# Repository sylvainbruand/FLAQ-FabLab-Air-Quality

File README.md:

# FLAQ XIAO — FabLab Air Quality

Projet académique de contrôle de la qualité de l’air dans les FabLabs, réalisé
avec une **Seeed Studio XIAO ESP32S3**. La carte acquiert les
capteurs, affiche les mesures sur OLED, enregistre l’historique sur microSD et
héberge elle-même un dashboard accessible depuis un téléphone ou un ordinateur.

[▶ Voir la vidéo de présentation FLAQ](FLAQ.mp4) — version MP4 de `FLAQ.avi`.

## Fonctions incluses

- actualisation des mesures toutes les 10 secondes ;
- lecture du SGP40 toutes les secondes avec compensation DHT20 ;
- trois graphiques avec axes indépendants ;
- moyenne glissante PM2.5 sur 24 heures ;
- indice intérieur FLAQ du vert au rouge ;
- alarme confirmée sur buzzer passif au niveau rouge ;
- journal persistant des dépassements avec durée, moyenne et maximum ;
- synthèse quotidienne et export CSV depuis le dashboard ;
- horodatage par RTC Grove PCF85063 ;
- correction NTP automatique lorsque le réseau donne accès à Internet ;
- point d’accès `FLAQ-XIAO` si aucun Wi-Fi n’est configuré ou disponible ;
- reprise de l’historique des dernières 24 heures après redémarrage ;
- navigation manuelle entre les quatre pages OLED avec le bouton Grove ;
- extinction de l’OLED après 20 secondes sans appui et réveil automatique ;
- déclaration manuelle d’une ventilation avec un second bouton Grove ;
- signalement de la ventilation sur le dashboard ;
- bandes temporelles claires sur les graphes pendant les périodes ventilées.

## Matériel

| Fonction | Référence | Connexion |
|---|---|---|
| Carte | Seeed Studio XIAO ESP32S3 | — |
| Hub | Grove 8-Channel I²C Hub TCA9548A | `D4/SDA`, `D5/SCL`, adresse `0x70` |
| CO₂ | SCD30 | I²C `0x61` |
| Particules | HM3301 | I²C `0x40` |
| VOC | SGP40 | I²C `0x59` |
| HCHO indicatif | Grove HCHO WSP2110 | analogique `D0`, via pont diviseur |
| Température/humidité | DHT20 | I²C `0x38` |
| Horloge | RTC Grove PCF85063 | I²C `0x51` |
| Affichage | OLED SSD1306 128×64 | I²C `0x3C` |
| Alarme | Grove Passive Buzzer 107020109 | `D1` |
| Navigation OLED | Grove Button (P) 111020000 | port `D7 / UART` |
| Ventilation | Grove Button (P) 111020000 | port `D0 / A0` |
| Stockage | Adafruit MicroSD Breakout+ 254 | SPI, CS sur `D2` |

Le câblage détaillé se trouve dans
[flaq_xiao/CABLAGE.md](flaq_xiao/CABLAGE.md).

Au démarrage, le firmware ouvre automatiquement les huit canaux du TCA9548A.
Cette configuration est possible car chaque capteur utilise une adresse I²C
différente. Elle se règle avec `FLAQ_I2C_MUX_*` dans `config.example.h`.

## Préparation de l’Arduino IDE

1. Installer le paquet de cartes **esp32 by Espressif Systems**.
2. Sélectionner **XIAO_ESP32S3**.
3. Activer la PSRAM en mode **OPI PSRAM**.
4. Sélectionner une taille Flash de **8 MB**.
5. Installer les bibliothèques :
   - U8g2 ;
   - Adafruit SGP40 Sensor, avec ses dépendances ;
   - SparkFun SCD30 Arduino Library ;
   - DHT20 de Rob Tillaart.

Le HM3301 est lu directement par le firmware via `Wire`, afin d’éviter
l’incompatibilité du type `u32` présente dans la bibliothèque Seeed 1.0.2 avec
les versions ESP32 récentes. En cas de trame incomplète ou de checksum invalide,
la lecture est retentée trois fois et le capteur est automatiquement replacé en
mode I2C. Les concentrations utilisées sont les valeurs « environnement
atmosphérique » du HM3301.

Les bibliothèques `WiFi`, `WebServer`, `ESPmDNS`, `SD`, `SPI` et `Wire` sont
fournies par le paquet ESP32.

## Configuration Wi-Fi

Le projet fonctionne immédiatement sans identifiants : la carte crée le réseau
`FLAQ-XIAO`, protégé par le mot de passe `flaq-air`. Une fois connecté à ce
réseau, ouvrir `http://192.168.4.1`.

Pour connecter la station au réseau local :

1. copier `config.h.example` sous le nom `config.h` ;
2. renseigner le nom et le mot de passe Wi-Fi ;
3. téléverser à nouveau le programme.

Le dashboard devient alors accessible à l’adresse IP affichée sur l’OLED et,
si le réseau l’autorise, à `http://flaq-xiao.local`.

`config.h` est ignoré par Git pour ne pas publier le mot de passe.

## Carte microSD

Utiliser une microSD High Endurance de 32 Go formatée en FAT32. La station crée :

- `/data/AAAAMMJJ.csv` : mesures d’une journée ;
- `/events.csv` : dépassements terminés.

La fenêtre glissante est maintenue en PSRAM. Au redémarrage, les fichiers du
jour courant et du jour précédent sont relus afin de reconstruire les dernières
24 heures, la moyenne PM2.5 et les périodes de ventilation. La colonne
`ventilation` vaut `1` lorsque la fenêtre ou la porte a été déclarée ouverte.

## Seuils

Tous les seuils se trouvent dans `config.example.h` et peuvent être redéfinis
dans `config.h`. L’indice global correspond au paramètre instantané le plus
défavorable parmi CO₂, VOC, HCHO estimé, PM2.5 et PM10.

Une alerte ou un événement nécessite trois mesures consécutives au-dessus du
seuil. Le retour utilise un seuil plus bas et trois confirmations, ce qui évite
les oscillations autour d’une limite.

Le seuil de la moyenne PM2.5 sur 24 heures produit un événement distinct. Il
n’est activé que lorsque la station dispose d’au moins 23 heures d’historique.

Ces seuils constituent un indicateur pédagogique FLAQ de qualité de l’air
intérieur ; ils ne remplacent pas un dispositif réglementaire ou certifié.

## Particularités du WSP2110

Le WSP2110 est désactivé par défaut avec `FLAQ_WSP2110_ENABLED 0`. Dans cet
état, D0 n'est pas lu, le dashboard affiche « non installé », le HCHO est
ignoré par l'indice et aucune alerte HCHO n'est créée. Quand le capteur et son
pont diviseur sont prêts, définir `FLAQ_WSP2110_ENABLED 1` dans `config.h`.

Le WSP2110 est un capteur MOS sensible à plusieurs gaz et solvants. La valeur
« HCHO estimé » en ppm sert donc à suivre une tendance après étalonnage ; ce
n’est pas une mesure sélective ou certifiée du formaldéhyde. Le capteur demande
au moins 120 heures de préchauffage avant son étalonnage initial.

Le module Grove fonctionne en 5 V alors que l’entrée analogique du XIAO est en
3,3 V. Sa sortie doit obligatoirement passer par le pont 15 kΩ / 20 kΩ décrit
dans `flaq_xiao/CABLAGE.md`. La constante `FLAQ_WSP2110_R0_RATIO` doit ensuite
être ajustée dans `config.h` avec la valeur obtenue en air propre stabilisé. Le
moniteur série affiche `WSP_Rs` et `ADC` pour faciliter cette opération.

## API embarquée

| Route | Rôle |
|---|---|
| `/` | dashboard |
| `/logo.png` | logo FLAQ et favicon |
| `/api/live` | dernière mesure et état technique |
| `/api/history?since=...&max=900` | historique sous-échantillonné |
| `/api/events?max=200` | journal des dépassements |
| `/api/events.csv` | téléchargement CSV |
| `/api/health` | mémoire et disponibilité du serveur |

## Organisation du dépôt

- [`flaq_xiao/`](flaq_xiao/) : station autonome XIAO ESP32S3 ;

## Fichiers du projet XIAO

- `flaq_xiao/flaq_xiao.ino` : firmware complet ;
- `flaq_xiao/dashboard.h` : interface web embarquée sans dépendance Internet ;
- `flaq_xiao/config.example.h` : valeurs par défaut et seuils ;
- `flaq_xiao/config.h.example` : modèle de configuration Wi-Fi ;
- `flaq_xiao/CABLAGE.md` : raccordement pas à pas ;
- `flaq_xiao/VERIFICATION.md` : procédure de mise en service.

## Vues du projet FLAQ

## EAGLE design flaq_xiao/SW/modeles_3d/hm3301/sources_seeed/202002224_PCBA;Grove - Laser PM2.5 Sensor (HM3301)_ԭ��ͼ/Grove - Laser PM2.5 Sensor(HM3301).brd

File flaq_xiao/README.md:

# FLAQ XIAO — FabLab Air Quality

Projet académique de contrôle de la qualité de l’air dans les FabLabs, réalisé
avec une **Seeed Studio XIAO ESP32S3**. La carte acquiert les
capteurs, affiche les mesures sur OLED, enregistre l’historique sur microSD et
héberge elle-même un dashboard accessible depuis un téléphone ou un ordinateur.

## Fonctions incluses

- actualisation des mesures toutes les 10 secondes ;
- lecture du SGP40 toutes les secondes avec compensation DHT20 ;
- trois graphiques avec axes indépendants ;
- moyenne glissante PM2.5 sur 24 heures ;
- indice intérieur FLAQ du vert au rouge ;
- alarme confirmée sur buzzer passif au niveau rouge ;
- journal persistant des dépassements avec durée, moyenne et maximum ;
- synthèse quotidienne et export CSV depuis le dashboard ;
- horodatage par RTC Grove PCF85063 ;
- correction NTP automatique lorsque le réseau donne accès à Internet ;
- point d’accès `FLAQ-XIAO` si aucun Wi-Fi n’est configuré ou disponible ;
- reprise de l’historique des dernières 24 heures après redémarrage.
- navigation manuelle entre les quatre pages OLED avec le bouton Grove ;
- extinction de l’OLED après 20 secondes sans appui et réveil automatique.
- déclaration manuelle d’une ventilation avec un second bouton Grove ;
- mode mute basculé en appuyant sur les deux boutons en même temps ;
- signalement de la ventilation sur le dashboard et éclaircissement des graphes.
- bandes temporelles claires sur les graphes pendant les périodes ventilées.

## Matériel

| Fonction | Référence | Connexion |
|---|---|---|
| Carte | Seeed Studio XIAO ESP32S3 | — |
| Hub | Grove 8-Channel I²C Hub TCA9548A | `D4/SDA`, `D5/SCL`, adresse `0x70` |
| CO₂ | SCD30 | I²C `0x61` |
| Particules | HM3301 | I²C `0x40` |
| VOC | SGP40 | I²C `0x59` |
| HCHO indicatif | Grove HCHO WSP2110 | analogique `D0`, via pont diviseur |
| Température/humidité | DHT20 | I²C `0x38` |
| Horloge | RTC Grove PCF85063 | I²C `0x51` |
| Affichage | OLED SSD1306 128×64 | I²C `0x3C` |
| Alarme | Grove Passive Buzzer 107020109 | `D1` |
| Navigation OLED + ventilation | Grove Dual Button | port `D7 / UART` (`D7` + `D6`) |
| Stockage | Adafruit MicroSD Breakout+ 254 | SPI, CS sur `D2` |

Le câblage détaillé se trouve dans [CABLAGE.md](CABLAGE.md).

Au démarrage, le firmware ouvre automatiquement les huit canaux du TCA9548A.
Cette configuration est possible car chaque capteur utilise une adresse I²C
différente. Elle se règle avec `FLAQ_I2C_MUX_*` dans `config.example.h`.

## Préparation de l’Arduino IDE

1. Installer le paquet de cartes **esp32 by Espressif Systems**.
2. Sélectionner **XIAO_ESP32S3**.
3. Activer la PSRAM en mode **OPI PSRAM**.
4. Sélectionner une taille Flash de **8 MB**.
5. Installer les bibliothèques :
   - U8g2 ;
   - Adafruit SGP40 Sensor, avec ses dépendances ;
   - SparkFun SCD30 Arduino Library ;
   - DHT20 de Rob Tillaart.

Le HM3301 est lu directement par le firmware via `Wire`, afin d’éviter
l’incompatibilité du type `u32` présente dans la bibliothèque Seeed 1.0.2 avec
les versions ESP32 récentes. En cas de trame incomplète ou de checksum invalide,
la lecture est retentée trois fois et le capteur est automatiquement replacé en
mode I2C. Les concentrations utilisées sont les valeurs « environnement
atmosphérique » du HM3301.

Les bibliothèques `WiFi`, `WebServer`, `ESPmDNS`, `SD`, `SPI` et `Wire` sont
fournies par le paquet ESP32.

## Configuration Wi-Fi

Le projet fonctionne immédiatement sans identifiants : la carte crée le réseau
`FLAQ-XIAO`, protégé par le mot de passe `flaq-air`. Une fois connecté à ce
réseau, ouvrir `http://192.168.4.1`.

Pour connecter la station au réseau local :

1. copier `config.h.example` sous le nom `config.h` ;
2. renseigner les noms et mots de passe des réseaux Wi-Fi dans
   `FLAQ_WIFI_NETWORKS` (une ligne par réseau) ;
3. téléverser à nouveau le programme.

Au démarrage, l’OLED affiche la liste configurée. Le bouton sur D7 passe au
réseau suivant et le bouton sur D6 valide le réseau affiché. Après la
validation, les deux boutons reprennent automatiquement leur fonctionnement
normal (pages OLED et ventilation). Si la connexion choisie échoue, la station
crée comme auparavant le point d’accès `FLAQ-XIAO`.

Le dashboard devient alors accessible à l’adresse IP affichée sur l’OLED et,
si le réseau l’autorise, à `http://flaq-xiao.local`.

`config.h` est ignoré par Git pour ne pas publier le mot de passe.

## Carte microSD

Utiliser une microSD High Endurance de 32 Go formatée en FAT32. La station crée :

- `/data/AAAAMMJJ.csv` : mesures d’une journée ;
- `/events.csv` : dépassements terminés.

La fenêtre glissante est maintenue en PSRAM. Au redémarrage, les fichiers du
jour courant et du jour précédent sont relus afin de reconstruire les dernières
24 heures, la moyenne PM2.5 et les périodes de ventilation. La colonne
`ventilation` vaut `1` lorsque la fenêtre ou la porte a été déclarée ouverte.

## Seuils

Tous les seuils se trouvent dans `config.example.h` et peuvent être redéfinis
dans `config.h`. L’indice global correspond au paramètre instantané le plus
défavorable parmi CO₂, VOC, HCHO estimé, PM2.5 et PM10.

Une alerte ou un événement nécessite trois mesures consécutives au-dessus du
seuil. Le retour utilise un seuil plus bas et trois confirmations, ce qui évite
les oscillations autour d’une limite.

Le seuil de la moyenne PM2.5 sur 24 heures produit un événement distinct. Il
n’est activé que lorsque la station dispose d’au moins 23 heures d’historique.

Ces seuils constituent un indicateur pédagogique FLAQ de qualité de l’air
intérieur ; ils ne remplacent pas un dispositif réglementaire ou certifié.

## Particularités du WSP2110

Le WSP2110 est lu sur D0 mais reste optionnel. S’il n’est pas branché, ou tant
qu’aucune lecture valide n’est détectée, le dashboard affiche « indisponible »,
le HCHO est ignoré par l’indice et aucune alerte HCHO n’est créée. Cette absence
n’empêche ni le démarrage ni le fonctionnement des autres capteurs.

Le WSP2110 est un capteur MOS sensible à plusieurs gaz et solvants. La valeur
« HCHO estimé » en ppm sert donc à suivre une tendance après étalonnage ; ce
n’est pas une mesure sélective ou certifiée du formaldéhyde. Le capteur demande
au moins 120 heures de préchauffage avant son étalonnage initial.

Le module Grove fonctionne en 5 V alors que l’entrée analogique du XIAO est en
3,3 V. Sa sortie doit obligatoirement passer par le pont 15 kΩ / 20 kΩ décrit
dans `CABLAGE.md`. La constante `FLAQ_WSP2110_R0_RATIO` doit ensuite être
ajustée dans `config.h` avec la valeur obtenue en air propre stabilisé. Le
moniteur série affiche `WSP_Rs` et `ADC` pour faciliter cette opération.

## API embarquée

| Route | Rôle |
|---|---|
| `/` | dashboard |
| `/logo.png` | logo FLAQ et favicon |
| `/api/live` | dernière mesure et état technique |
| `/api/history?since=...&max=900` | historique sous-échantillonné |
| `/api/events?max=200` | journal des dépassements |
| `/api/events.csv` | téléchargement CSV |
| `/api/health` | mémoire et disponibilité du serveur |

## Fichiers du projet

- `flaq_xiao.ino` : firmware complet ;
- `dashboard.h` : interface web embarquée sans dépendance Internet ;
- `flaq_logo.png` et `flaq_logo.h` : logo optimisé et ressource embarquée ;
- `config.example.h` : valeurs par défaut et seuils ;
- `config.h.example` : modèle de configuration Wi-Fi ;
- `CABLAGE.md` : raccordement pas à pas ;
- `VERIFICATION.md` : procédure de mise en service.

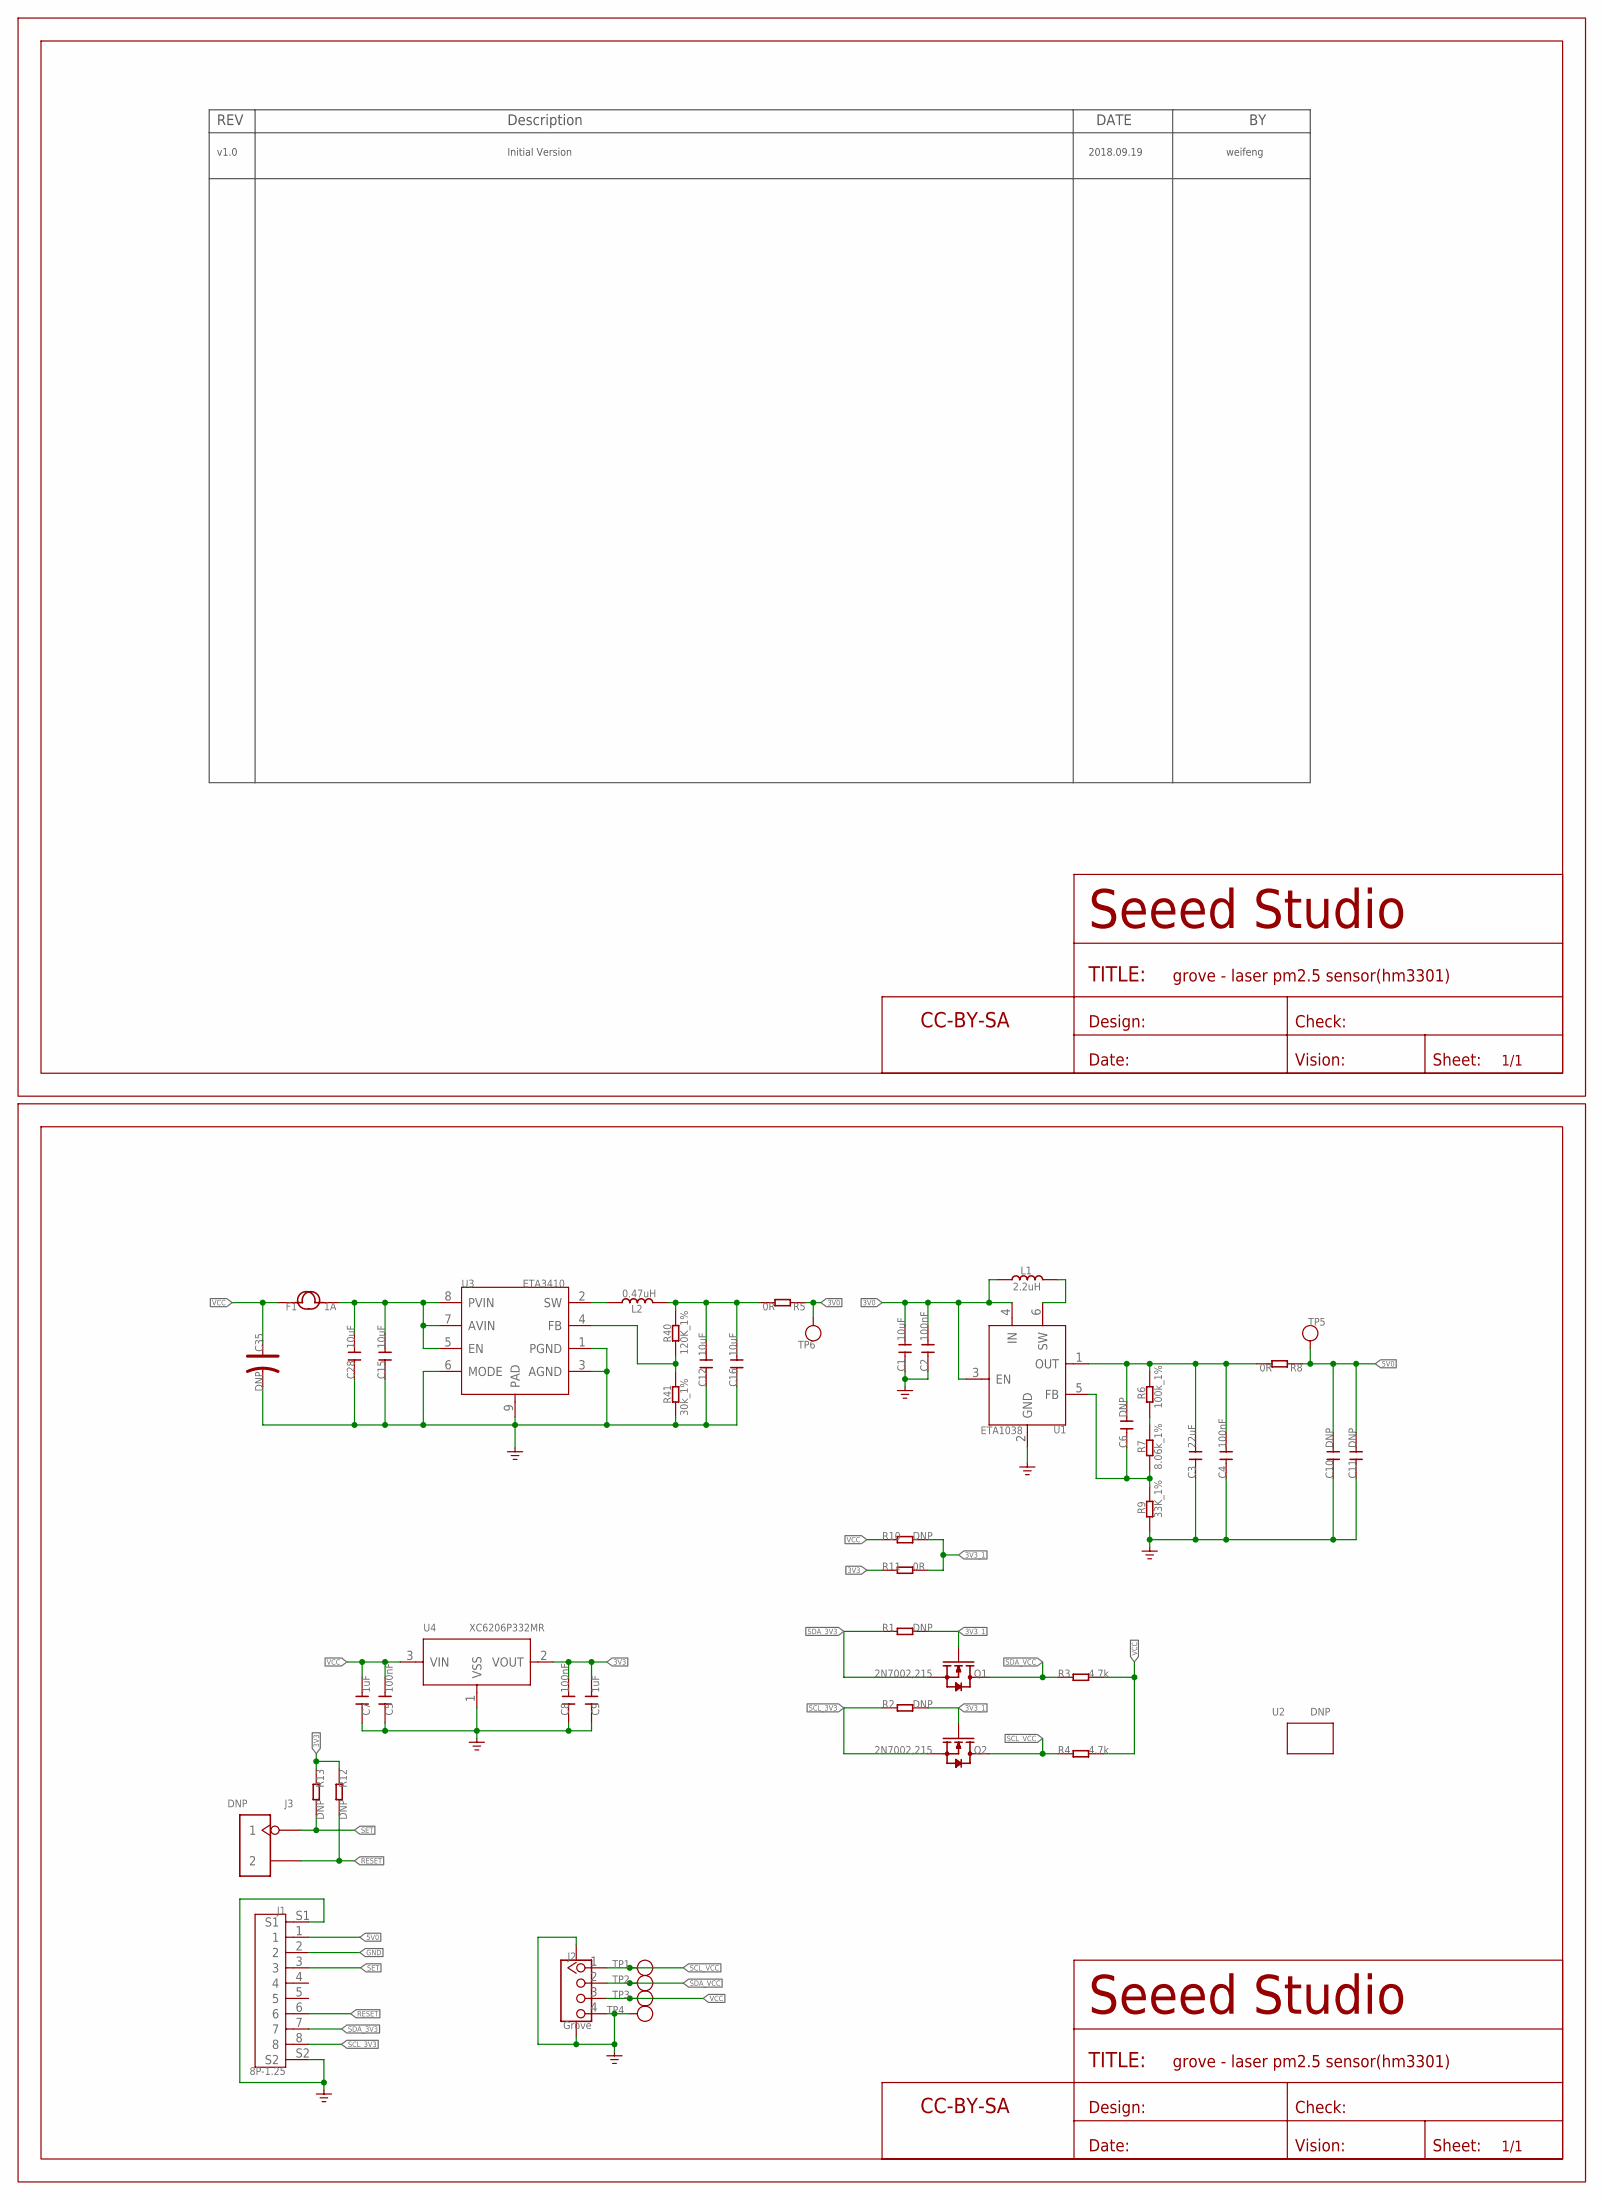
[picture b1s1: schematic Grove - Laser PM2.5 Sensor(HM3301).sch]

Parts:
C1, C12, C15, C16, C28: 10uF; C0603
C2, C4, C5, C8: 100nF; C0603
C3: 22uF; C0805
C6, C11: DNP; C0603
C7, C9: 1uF; C0603
C10: DNP; C0805
C35: DNP; AVX-B
F1: 1A; F0805
FR1: SEEEDSTUDIO-OPEN-SCH-FRAME; SEEEDSTUDIO-PCB-FRAME
J1: 8P-1.25; HEADER8+2P-SMD-1.25-15X3.5MM
J2: Grove; HW4-SMD-2.0-90D
J3: DNP; H2-2.54
L1: 2.2uH; L0806
L2: 0.47uH; L201610
Q1, Q2: 2N7002,215; SOT-23
R1, R2, R10, R12, R13: DNP; R0603
R3, R4: 4.7k; R0603
R5, R8, R11: 0R; R0603
R6: 100k_1%; R0603
R7: 8.06k_1%; R0603
R9: 33K_1%; R0603
R40: 120K_1%; R0603
R41: 30k_1%; R0603
TP1, TP2, TP3, TP4, TP5, TP6: TEST-POINT'4545'; TP-D45MIL
U1: ETA1038; SOT-23-6
U2: DNP; GROVE-80X40MM
U3: ETA3410; DFN8G-0.5-2X2MM
U4: XC6206P332MR; SOT-23
U$4: SEEEDSTUDIO-OPEN-SCH-FRAME; SEEEDSTUDIO-PCB-FRAME

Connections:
3V0: C1.2, C2.2, L1.1, R5.1, TP6.T, U1.3 (EN), U1.4 (IN)
3V3: C8.2, C9.2, R11.1, R12.1, R13.1, U4.2 (VOUT)
3V3_1: Q1.1 (G), Q2.1 (G), R1.2, R2.2, R10.2, R11.2
5V0: C10.2, C11.2, J1.1, R8.1, TP5.T
GND: C1.1, C2.1, C3.1, C4.1, C5.1, C7.1, C8.1, C9.1, C10.1, C11.1, C12.1, C15.1, C16.1, C28.1, C35.-, J1.2, J1.S1, J1.S2, J2.4, J2.SS1, J2.SS2, R9.2, R41.1, TP4.T, U1.2 (GND), U3.1 (PGND), U3.3 (AGND), U3.6 (MODE), U3.9 (PAD), U4.1 (VSS)
unnamed: C15.2, C28.2, F1.2, U3.5 (EN), U3.7 (AVIN), U3.8 (PVIN)
unnamed: L1.2, U1.6 (SW)
unnamed: C3.2, C4.2, C6.2, R6.1, R8.2, U1.1 (OUT)
unnamed: R6.2, R7.1
unnamed: C6.1, R7.2, R9.1, U1.5 (FB)
unnamed: R40.1, R41.2, U3.4 (FB)
unnamed: L2.1, U3.2 (SW)
unnamed: C12.2, C16.2, L2.2, R5.2, R40.2
RESET: J1.6, J3.2, R12.2
SCL_3V3: J1.8, Q2.2 (S), R2.1
SCL_VCC: J2.1, Q2.3 (D), R4.1, TP1.T
SDA_3V3: J1.7, Q1.2 (S), R1.1
SDA_VCC: J2.2, Q1.3 (D), R3.1, TP2.T
SET: J1.3, J3.1, R13.2
VCC: C5.2, C7.2, C35.+, F1.1, J2.3, R3.2, R4.2, R10.1, TP3.T, U4.3 (VIN)

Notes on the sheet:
v1.0
Initial Version
2018.09.19
weifeng

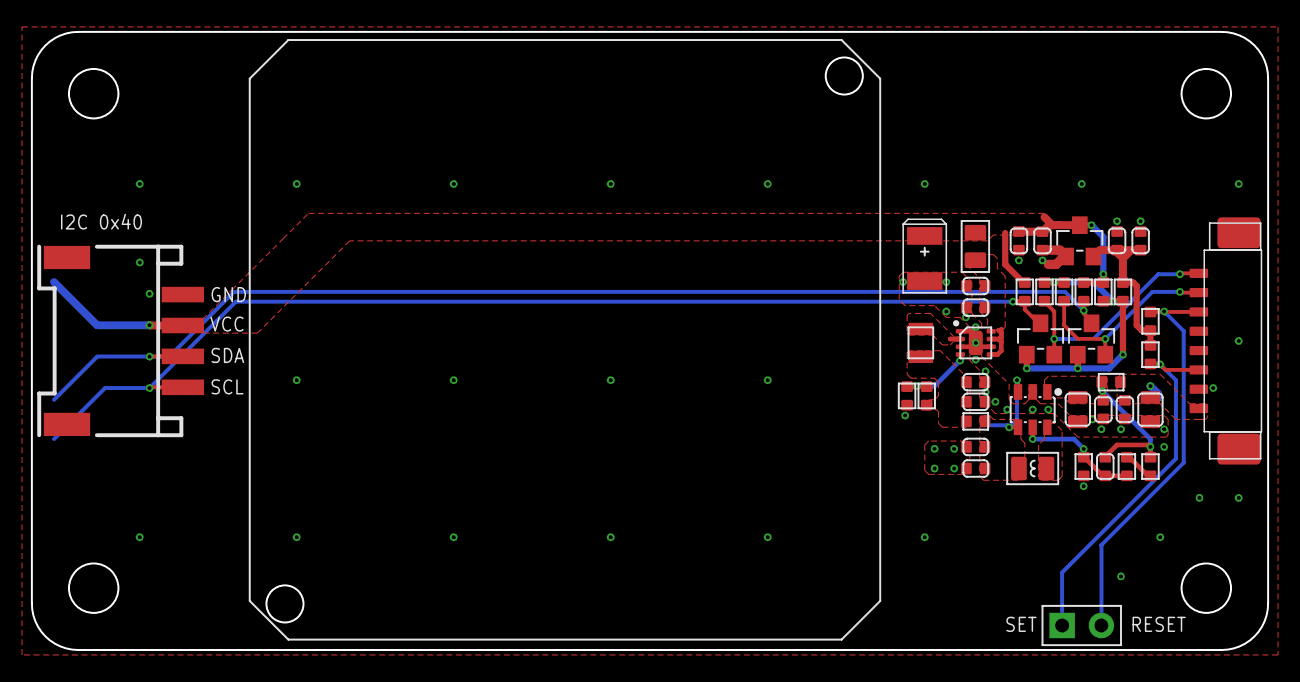
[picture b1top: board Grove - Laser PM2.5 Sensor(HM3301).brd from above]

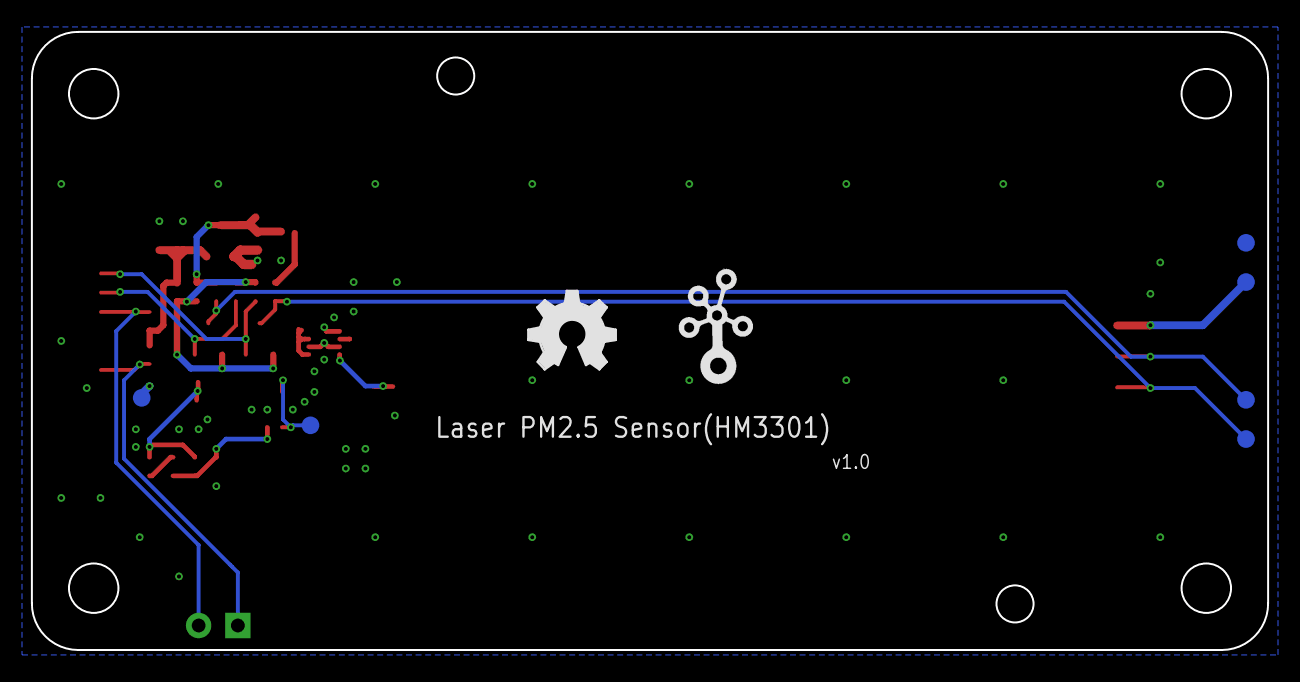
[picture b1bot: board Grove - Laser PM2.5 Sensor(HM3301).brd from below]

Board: 2 copper layers, 80.0 x 40.0 mm, 53 parts (8 on the bottom side), 20 nets.

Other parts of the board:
U$5: OSHW_FILLX200_NOTEXT
U$7: TWIGLOGO

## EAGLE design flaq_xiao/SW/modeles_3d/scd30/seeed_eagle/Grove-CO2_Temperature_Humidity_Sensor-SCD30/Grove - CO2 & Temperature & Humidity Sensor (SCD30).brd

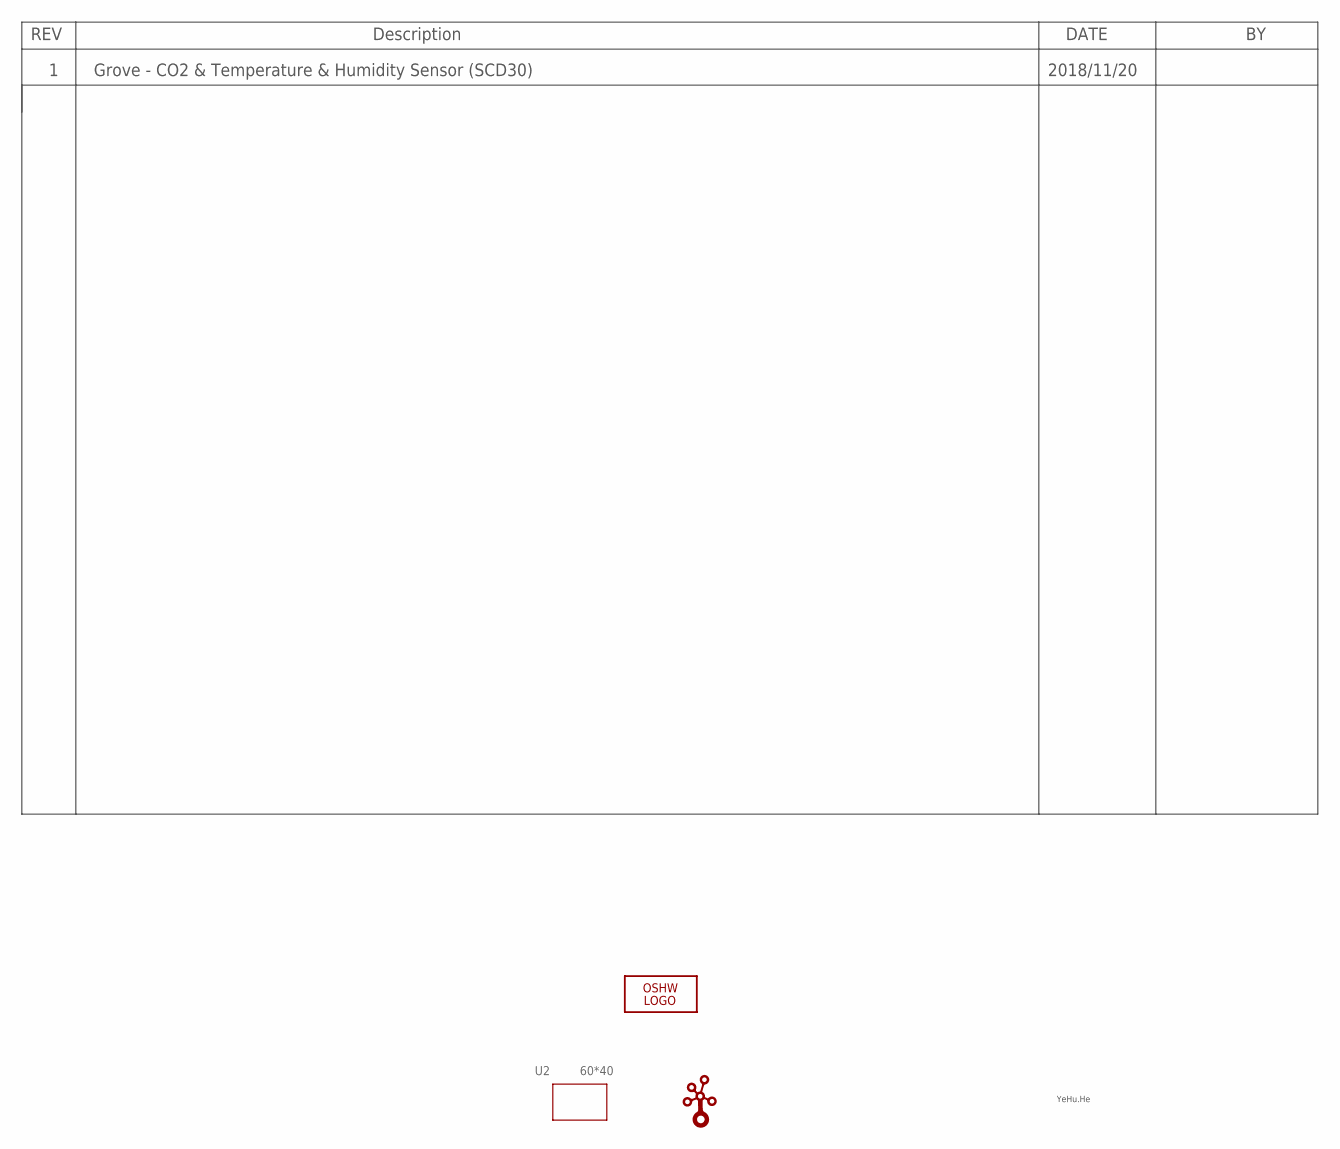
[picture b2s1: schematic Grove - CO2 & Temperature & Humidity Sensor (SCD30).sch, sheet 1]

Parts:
LOGO1: LOGO-OSHW-FILLX0200-NT; OSHW_FILLX200_NOTEXT
U2: 60*40; GROVE-60X40MM
U$4: LOGO-GROVE; GROVE-SILK-BIG

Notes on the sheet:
Grove - CO2 & Temperature & Humidity Sensor (SCD30)
2018/11/20
YeHu.He

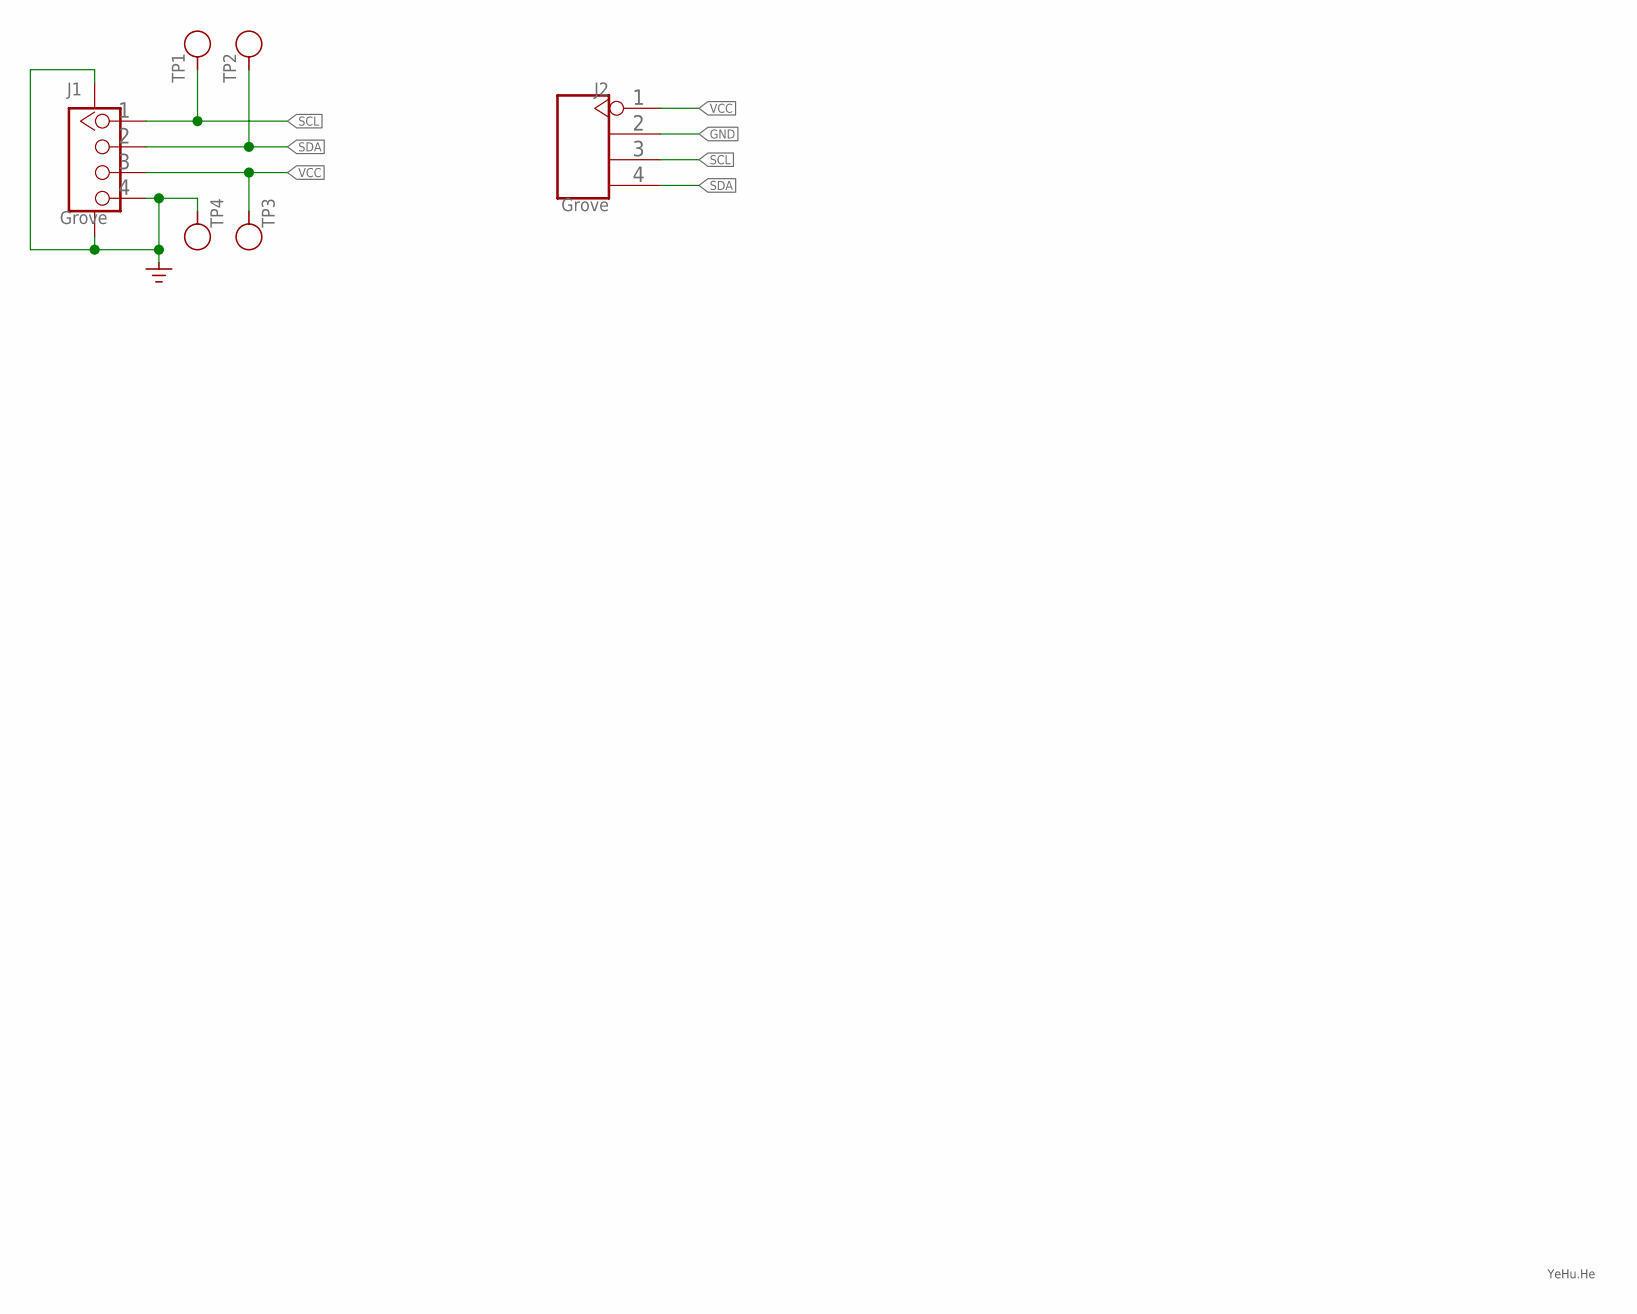
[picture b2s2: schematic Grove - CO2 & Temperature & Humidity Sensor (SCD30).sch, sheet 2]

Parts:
J1: Grove; HW4-SMD-2.0-90D
J2: Grove; H4-2.54
TP1, TP2, TP3, TP4: Test; TP-D45MIL

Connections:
GND: J1.4, J1.SS1, J1.SS2, J2.2, TP4.T
SCL: J1.1, J2.3, TP1.T
SDA: J1.2, J2.4, TP2.T
VCC: J1.3, J2.1, TP3.T

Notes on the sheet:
YeHu.He

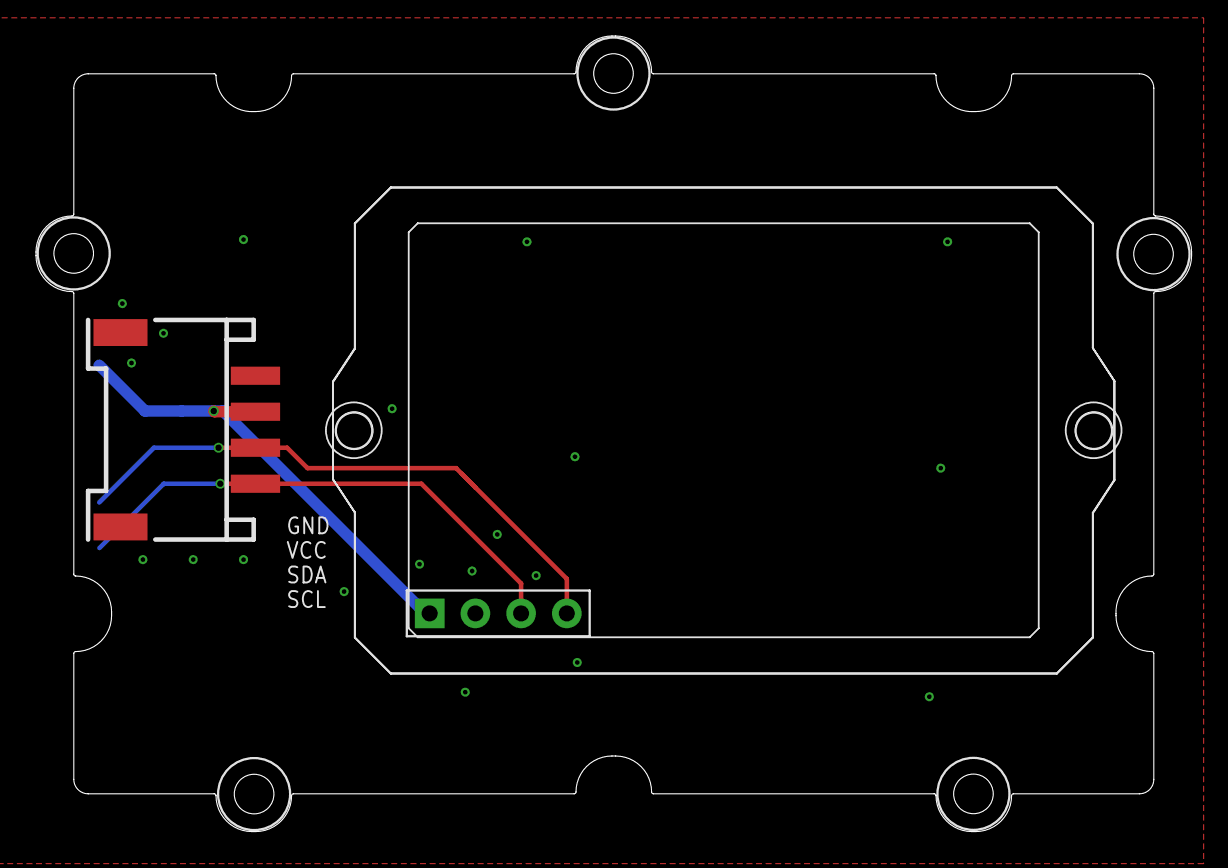
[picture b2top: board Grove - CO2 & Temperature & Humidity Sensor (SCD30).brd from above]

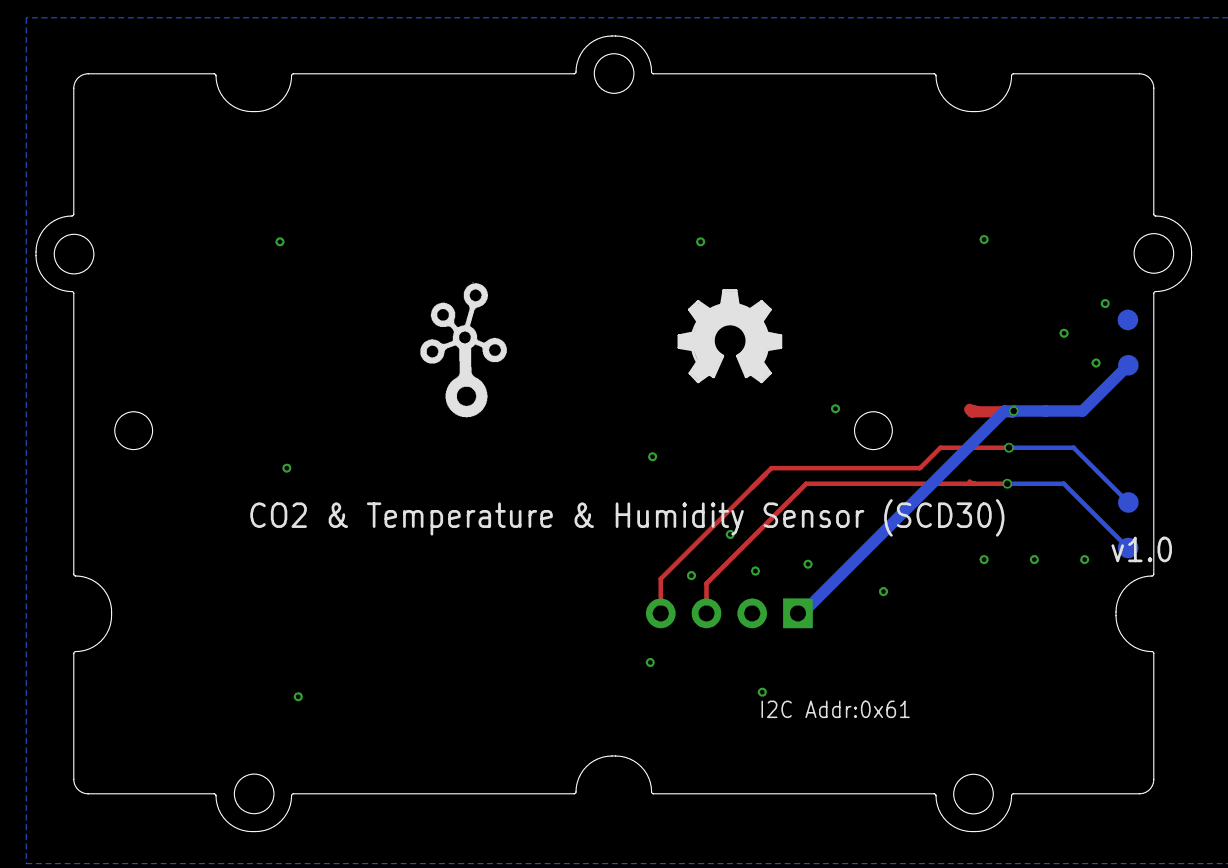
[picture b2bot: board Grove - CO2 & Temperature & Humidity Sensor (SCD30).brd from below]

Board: 2 copper layers, 64.2 x 44.2 mm, 9 parts (6 on the bottom side), 4 nets.

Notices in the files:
parts and their libraries:
moudle-new: This work is licensed under the Creative Commons Attribution 4.0 International License.
To view a copy of this license,visit:
http://creativecommons.org/licenses/by-sa/4.0
moudle-new: CC-BY-SA
